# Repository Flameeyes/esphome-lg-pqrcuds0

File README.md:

<!--
SPDX-FileCopyrightText: 2021 Diego Elio Pettenò

SPDX-License-Identifier: 0BSD
-->

# LG PQRCUDS0 compatible ESPHome Component

This repository contains the source code and the EAGLE design files for using
[ESPHome](https://esphome.io/) to control a LG air conditioning unit that uses
the PQRCUDS0 control panel.

The source code and an example configuration package are in the `esphome/`
directory, while the `eagle/` directory has the PCB design files.

Note that this project is neither endorsed, nor sponsored, by either of LG
or the ESPHome project.

You can find details of the implementation and some of the choices made in the
design on my blog: https://flameeyes.blog/tag/lg-pqrcuds0/

See also:

* Python utilities to emulate the panel and engine at
    <https://github.com/Flameeyes/lg-PQRCUDS0-emu>
* [Saleae Logic](https://www.saleae.com/) high-level analyzer for the
  protocol, at <https://github.com/Flameeyes/saleae-extension-LG-PQRCUDS0>

## Features

The custom component needs [Home Assistant](https://www.home-assistant.io/),
to provide a reference temperature, as it does not provide its own temperature
sensor.

Once provided a reference temperature sensor, the component supports the
following features, tested on my flat's HVAC system (LG ARNU07GB1G2):

* Cool, heat, fan-only, dehumidifer, and heat-cool modes, with two-point set
  temperature.

* Fan speed selection (low/medium/high), including "off" speed for idling in
  heat-cool mode.

## Board Revision History

### Rev 1

Original production design. It provided support to host the panel to the side
for going back to the panel on request, with a cutoff switch.

The cutoff had problems with holding the HVAC unit and the panel in sync when
switching away from the ESP32, so it never really worked.

The other reason to keep te panel powered up would have been to maintain a
readout of the temperature from the panel's on-board temperature sensor, but
it does not appear to be very reliable or useful, being able to report only
between 18C and 30C.

### Rev 2

A size- and cost-reduced variant of the original board, with the same logic
design, but without the secondary bus (and related components), and replacing
the cutoff switch with a pushbutton that turns off the whole board.

The bus connector is now on the back of the board, to make it easier to access
from the wall itself.

## License

Both the custom component and the EAGLE design files are released under the
permissive 0BSD license. This means you can reuse them pretty much as you may
want to.

Do note that ESPHome libraries are licensed under GNU GPLv3, so combining them
with logic in the components is still subject to the full license.

## Boxes

The `boxes/` directory contains 3D printable files for a box compatible with
the rev2 board.

Since this is literally my first 3D design, take it with a grain of salt,
it particularly suffers from the following minor issues:

* The cover vents on the top are not shaped to keep into consideration the
  registration corners.
* The central screw is unnecessary as (at least with Nylon SLS print) it is
  perfectly possible to keep the box closed by friction-fitting it.
* There should be a little more clearance for the ESP32 module, by raising
  the top of the cover.
* There's no compatible cap to fit into the pushbutton. A different strategy
  should be pursued.
* The keyholes should be more tolerant, as screws are often not quite aligned
  as they should be.

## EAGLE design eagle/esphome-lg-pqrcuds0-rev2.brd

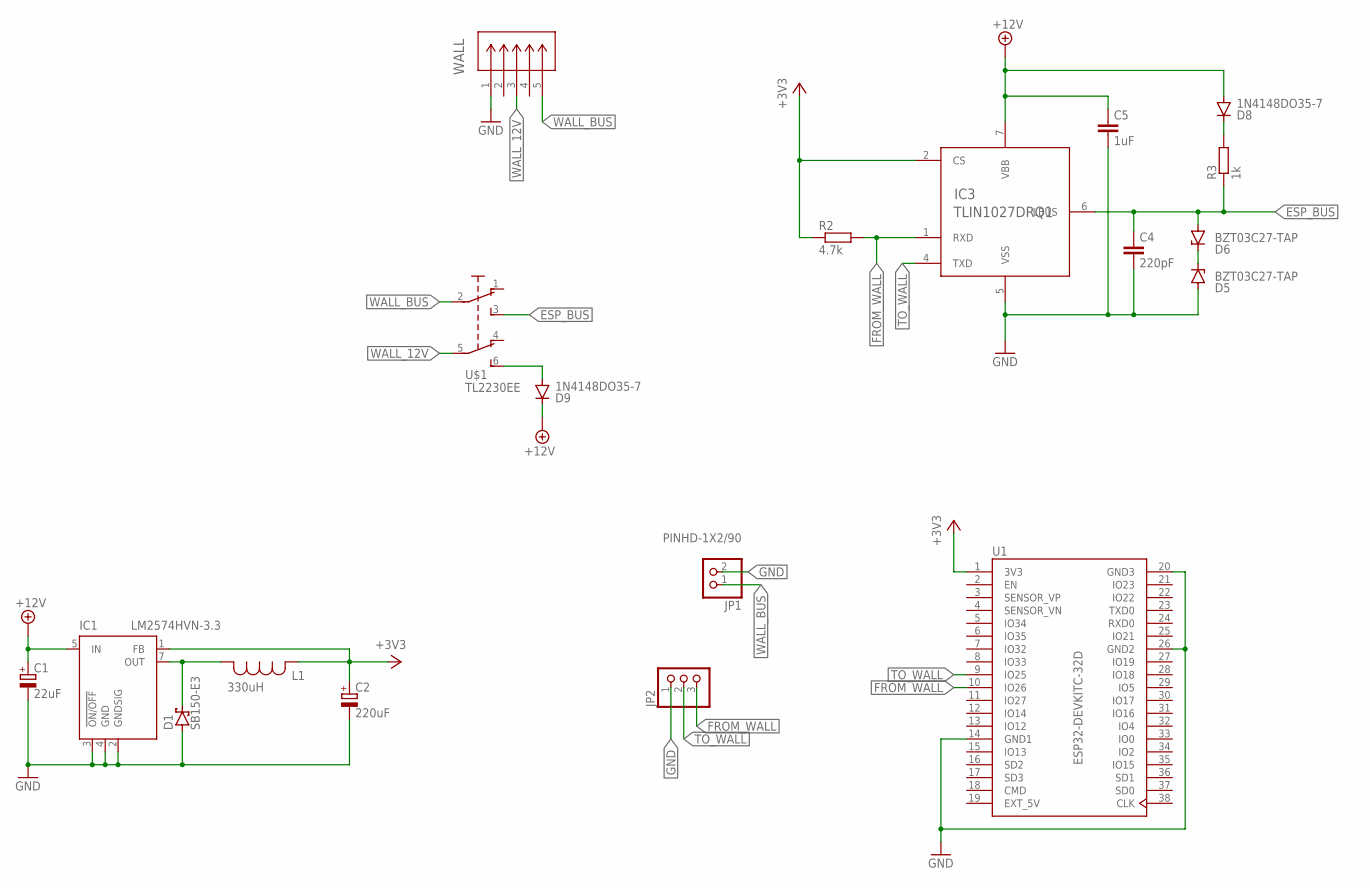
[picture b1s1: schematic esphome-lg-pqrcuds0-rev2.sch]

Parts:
C1: 22uF; E2,5-6
C2: 220uF; E2,5-6E
C4: 220pF; C050-025X075
C5: 1uF; C050-025X075
D1: SB150-E3; DO35-7
D5, D6: BZT03C27-TAP; SOD57Z10
D8, D9: 1N4148DO35-7; DO35-7
IC1: LM2574HVN-3.3; DIL08
IC3: TLIN1027DRQ1; SOIC8
JP1: PINHD-1X2/90; 1X02/90
JP2: PINHD-1X3/90; 1X03/90
L1: 330uH; AIAP-02_ABR
R2: 4.7k; 0204/7
R3: 1k; 0204/7
U1: ESP32-DEVKITC-32D; MODULE_ESP32-DEVKITC-32D
U$1: TL2230EE; TL2230
WALL: S5B-ZR(LF)(SN); CONN_S5B-ZR_JST

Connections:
+3V3: C2.+, IC1.1 (FB), IC3.2 (CS), L1.2, R2.1, U1.1 (3V3)
+12V: C1.+, C5.1, D8.A, D9.C, IC1.5 (IN), IC3.7 (VBB)
ESP_BUS: C4.1, D6.A, IC3.6 (LBUS), R3.1, U$1.3 (S)
EXT_5V: U1.19 (EXT_5V)
FROM_WALL: IC3.1 (RXD), JP2.3, R2.2, U1.10 (IO26)
GND: C1.-, C2.-, C4.2, C5.2, D1.A, D5.A, IC1.2 (GNDSIG), IC1.3 (!ON/OFF), IC1.4 (GND), IC3.5 (VSS), JP1.2, JP2.1, U1.14 (GND1), U1.20 (GND3), U1.26 (GND2), WALL.1
unnamed: D9.A, U$1.6 (S1)
unnamed: D1.C, IC1.7 (OUT), L1.1
unnamed: D8.C, R3.2
unnamed: D5.C, D6.C
TO_WALL: IC3.4 (TXD), JP2.2, U1.9 (IO25)
WALL_12V: U$1.5 (P1), WALL.3
WALL_BUS: JP1.1, U$1.2, WALL.5

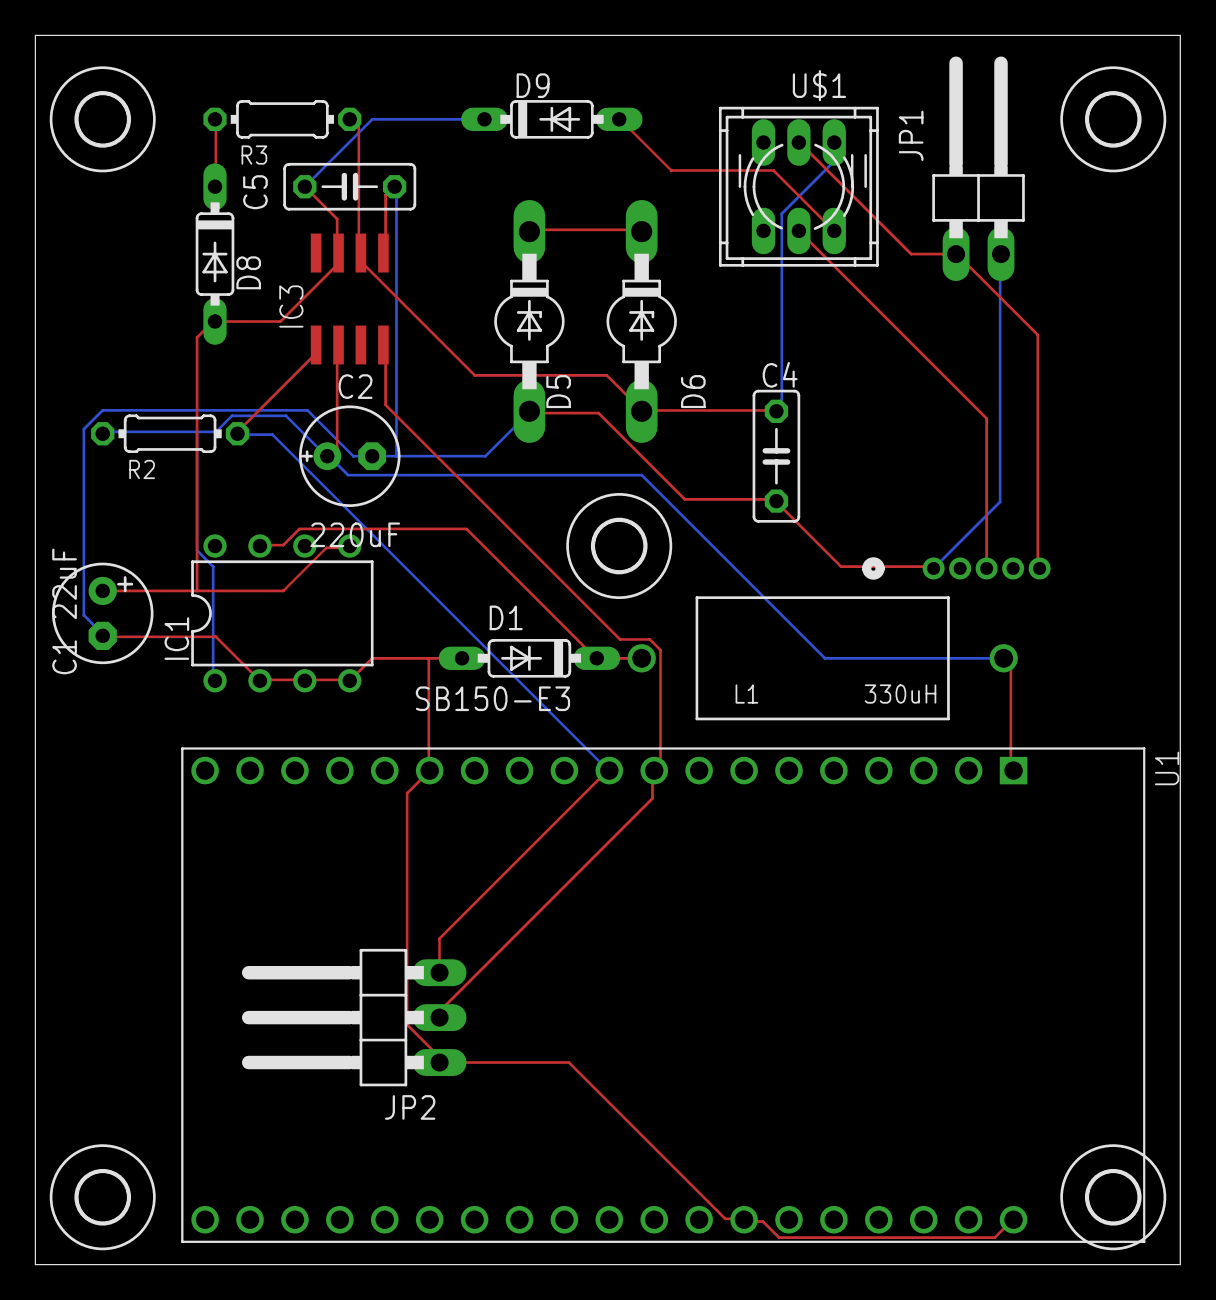
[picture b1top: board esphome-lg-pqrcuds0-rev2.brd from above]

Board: 2 copper layers, 64.8 x 69.5 mm, 24 parts (1 on the bottom side), 12 nets.

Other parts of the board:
U$2, U$3, U$4, U$5, U$6: 2,8

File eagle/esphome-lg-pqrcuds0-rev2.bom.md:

<!--
SPDX-FileCopyrightText: 2021 Diego Elio Pettenò

SPDX-License-Identifier: 0BSD
-->

# Bill Of Material for esphome-lg-pqrcuds0-rev1

Note: approximate cost applied to based on Digikey on 2021-08-01.

Prices are read in GBP before VAT, and for a single item.

| Quantity | Code               | Cost Per Unit | Total Cost |
| -------- | ------------------ | ------------- | ---------- |
| 1        | S5B-ZR(LF)(SN)     | £0.21         | £0.21      |
| 2        | 1N4148             | £0.07         | £0.14      |
| 1        | TL2230EEF140       | £0.64         | £0.64      |
| 1        | TLIN1027DRQ1       | £0.76         | £0.76      |
| 2        | BZT03C27-TAP       | £0.47         | £0.94      |
| 1        | FG28X5R1H105KRT06  | £0.27         | £0.27      |
| 1        | K221K10X7RF5UH5    | £0.14         | £0.14      |
| 1        | 4.7kΩ resistor     | £0.0034       | £0.0034    |
| 1        | 1kΩ resistor       | £0.00345      | £0.00345   |
| 1        | LM2574-3.3YN       | £1.22         | £1.22      |
| 1        | SB150-E3           | £0.29         | £0.29      |
| 1        | A759EK226M1JAAE054 | £0.39         | £0.39      |
| 1        | 860020474012       | £0.16         | £0.16      |
| 1        | AIAP-02-331K       | £0.49         | £0.49      |
| 2        | PPTC191LFBN-RC     | £0.84         | £1.68      |
| 1        | ESP32-DEVKITC-32D  | £7.16         | £7.16      |

Total: £14.50

## Cost Saving Ideas

The BZT03C27-TAP pair could be replaced with an integrated TVS diode like the
MMBZ27VALT3G (though surface mount) for £0.16.

The ESP32-DEVKIT-32D could be replaced with a WROOM module and the correct
passives, which would probably bring down the main cost by £5 or so between
the module itself, and the sockets.

The LM2574-3.3YN could be replaced with a linear regulator, given that the
panel no longer needs to be supplied in parallel.

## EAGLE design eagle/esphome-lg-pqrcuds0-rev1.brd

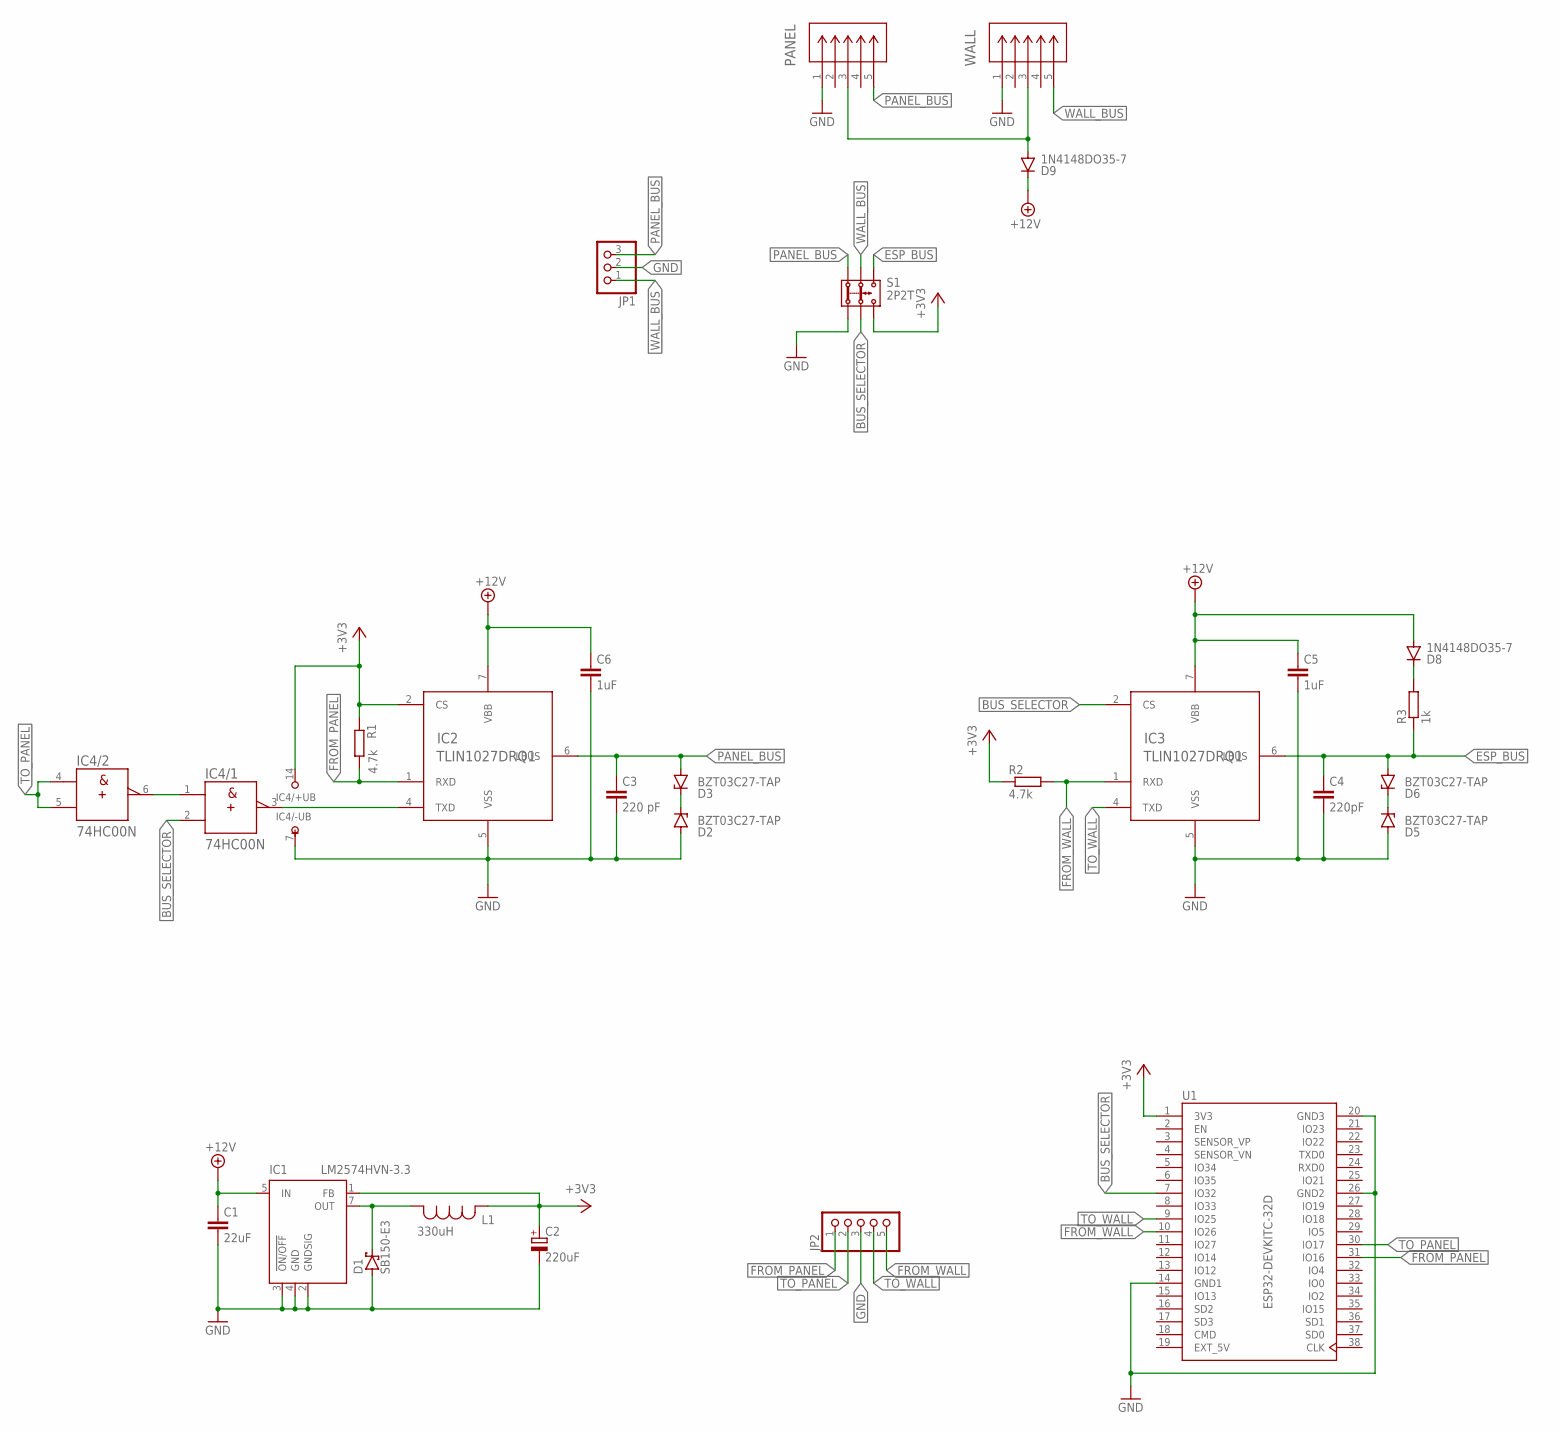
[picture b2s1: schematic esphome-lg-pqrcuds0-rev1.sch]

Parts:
C1: 22uF; C050-025X075
C2: 220uF; E2,5-6E
C3: 220 pF; C050-025X075
C4: 220pF; C050-025X075
C5, C6: 1uF; C050-025X075
D1: SB150-E3; DO35-7
D2, D3, D5, D6: BZT03C27-TAP; SOD57Z10
D8, D9: 1N4148DO35-7; DO35-7
IC1: LM2574HVN-3.3; DIL08
IC2, IC3: TLIN1027DRQ1; SOIC8
IC4: 74HC00N; DIL14
JP1: PINHD-1X3/90; 1X03/90
JP2: PINHD-1X5/90; 1X05/90
L1: 330uH; AIAP-02_ABR
PANEL: S5B-ZR(LF)(SN); CONN_S5B-ZR_JST
R1, R2: 4.7k; 0204/7
R3: 1k; 0204/7
S1: 2P2T
U1: ESP32-DEVKITC-32D; MODULE_ESP32-DEVKITC-32D
WALL: S5B-ZR(LF)(SN); CONN_S5B-ZR_JST

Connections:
+3V3: C2.+, IC1.1 (FB), IC2.2 (CS), IC4.14 (+UB), L1.2, R1.1, R2.1, S1.3.2, U1.1 (3V3)
+12V: C1.1, C5.1, C6.1, D8.A, D9.C, IC1.5 (IN), IC2.7 (VBB), IC3.7 (VBB)
BUS_SELECTOR: IC3.2 (CS), IC4.2 (B), S1.2.2, U1.7 (IO32)
ESP_BUS: C4.1, D6.A, IC3.6 (LBUS), R3.1, S1.3.1
EXT_5V: U1.19 (EXT_5V)
FROM_PANEL: IC2.1 (RXD), JP2.1, R1.2, U1.31 (IO16)
FROM_WALL: IC3.1 (RXD), JP2.5, R2.2, U1.10 (IO26)
GND: C1.2, C2.-, C3.2, C4.2, C5.2, C6.2, D1.A, D2.A, D5.A, IC1.2 (GNDSIG), IC1.3 (!ON/OFF), IC1.4 (GND), IC2.5 (VSS), IC3.5 (VSS), IC4.7 (-UB), JP1.2, JP2.3, PANEL.1, S1.1.2, U1.14 (GND1), U1.20 (GND3), U1.26 (GND2), WALL.1
unnamed: D1.C, IC1.7 (OUT), L1.1
unnamed: D8.C, R3.2
unnamed: IC2.4 (TXD), IC4.3 (Y)
unnamed: IC4.1 (A), IC4.6 (Y)
unnamed: D9.A, PANEL.3, WALL.3
unnamed: D2.C, D3.C
unnamed: D5.C, D6.C
PANEL_BUS: C3.1, D3.A, IC2.6 (LBUS), JP1.3, PANEL.5, S1.1.1
TO_PANEL: IC4.4 (A), IC4.5 (B), JP2.2, U1.30 (IO17)
TO_WALL: IC3.4 (TXD), JP2.4, U1.9 (IO25)
WALL_BUS: JP1.1, S1.2.1, WALL.5

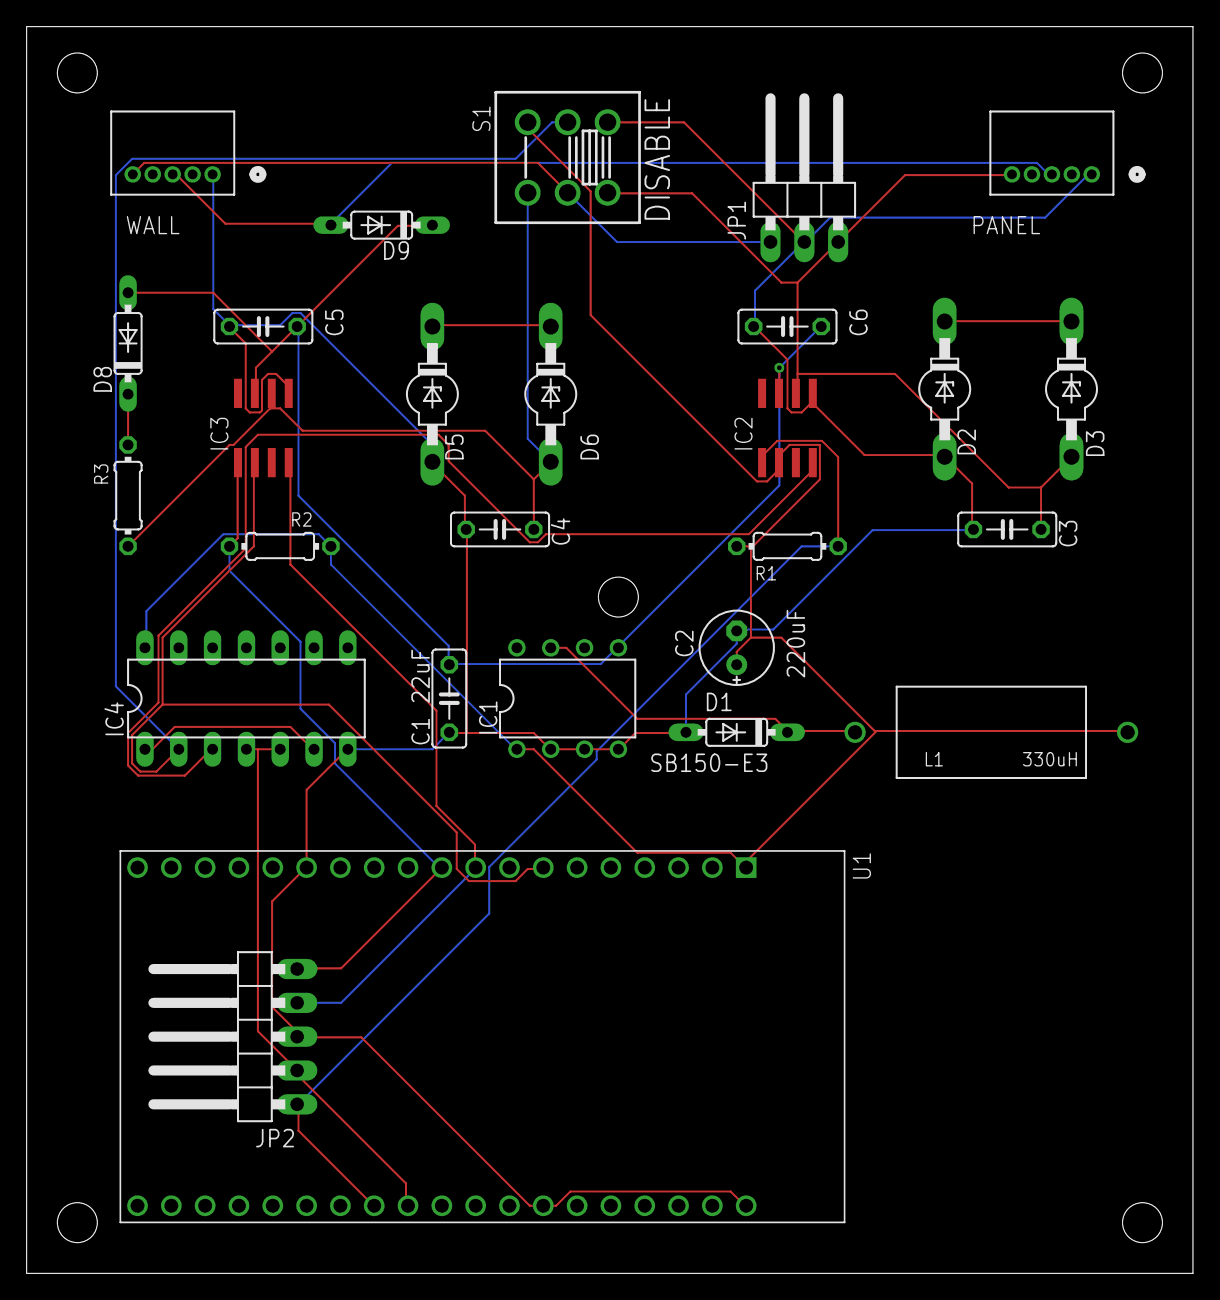
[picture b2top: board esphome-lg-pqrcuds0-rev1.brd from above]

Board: 2 copper layers, 87.6 x 93.6 mm, 27 parts (0 on the bottom side), 18 nets.

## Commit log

2021-07-29 Initial commit
    This imports the boards I actually had printed with no changes,
    which is not great because the silkscreen is missing, but for now
    I'm just going to "code dump" this here.
2021-07-31 Add missing license headers.
2021-07-31 Add missing LICENSE file.
2021-07-31 Ignore backup files created by EAGLE.
2021-07-31 Add a photo, some notes about the board design.
2021-07-31 Describe the supported features.
2021-08-01 Add a Bill-of-Materials.
2021-08-14 Add a note on the model of HVAC this was tested with.
2021-10-01 Introduce rev2 of the replacement board.
    The new revision of the board has fewer "dead" features, but is also half the size.
    It only includes a single bus, because the panel itself is not useful, and it has a power button instead of a toggle.
2021-10-01 Add STL files for the box.
2022-09-11 esphome: remove compile warnings by throwing an errors.
    There is no chance for these switch statements to have the values that
    the compiler complains about, but having the default case this can be
    avoided entirely.
2022-09-11 esphome: replace the deprecated hexencode() call.
2022-09-11 esphome: define the logger TAG at top-level.
2022-12-11 Rework hystheresis to correctly handle both heat and cool.
    The logic is a bit complicated, but we want to make sure we don't short-cycle the HVAC.
2022-12-11 Ignore venv (for pre-commit.)
2022-12-17 Add basic pre-commit support.
2022-12-17 Reformat with VSCode.
2022-12-17 Compensate for possible de-syncs.
    This might happen more likely when updating ESPHome.
2022-12-18 Use less noisy code to always fetch the serial.
    There seem to be a one cycle delay between sending a message and receiving the answer.
    Make sure that the data is always fetched in full.
2023-05-29 esphome config: update example to modern standard.
    This switches the example over to use ESP-IDF
    as well as using friendly names.
    It also includes a little documentation on how
    to configure the substitutions.
2023-10-29 Add more "sourcy" versions of the box itself.
    Instead of just including the generated STL, this *should* include the whole Fusion 360 history.
    And the 3MF should be more appropriate to make edits to, if needed.
2023-10-29 Use the more specific blog tag.
    That way if I ever talk about something _else_ from LG it won't get mixed up.

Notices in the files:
parts and their libraries:
COPYRIGHT: Copyright (C) 2018 Accelerated Designs. All rights reserved
